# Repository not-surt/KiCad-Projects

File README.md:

# KiCad-Projects

CC0 unless otherwise stated in subdirectory.

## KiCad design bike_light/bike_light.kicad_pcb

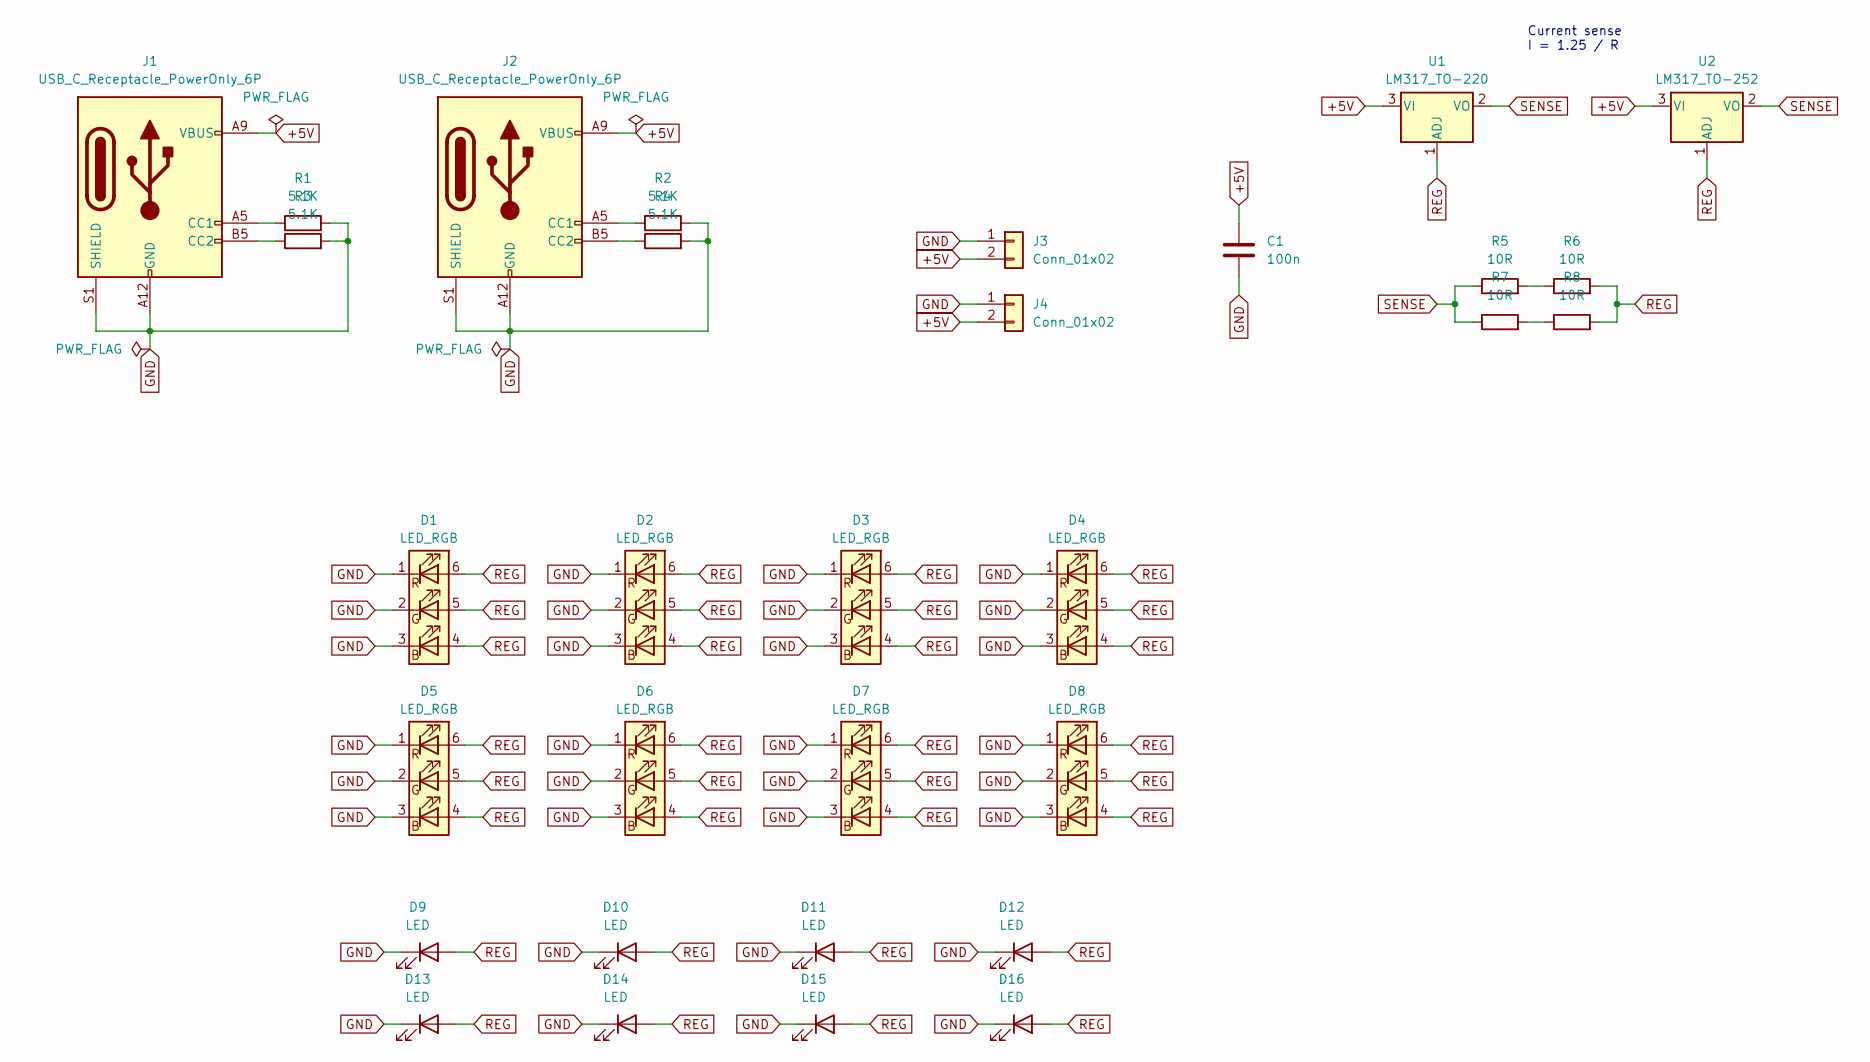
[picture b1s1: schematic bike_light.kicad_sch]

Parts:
C1: 100n; C_0805_2012Metric_Pad1.18x1.45mm_HandSolder
D1, D2, D3, D4, D5, D6, D7, D8: LED_RGB; LED_RGB_5050-6
D9, D10, D11, D12, D13, D14, D15, D16: LED; LED_Rectangular_W7.62mm_H4.55mm_P5.08mm_R3
J1, J2: USB_C_Receptacle_PowerOnly_6P; TYPE-C-31-M-17_handsolder
J3, J4: Conn_01x02; SolderWire-0.75sqmm_1x02_P4.8mm_D1.25mm_OD2.3mm_Relief
R1, R2, R3, R4: 5.1K; R_0805_2012Metric_Pad1.20x1.40mm_HandSolder
R5, R6, R7, R8: 10R; R_0805_2012Metric_Pad1.20x1.40mm_HandSolder
U1: LM317_TO-220; TO-220-3_Horizontal_TabDown
U2: LM317_TO-252; TO-252-2

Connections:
+5V: C1.1, J1.A9 (VBUS), J1.B9 (VBUS), J2.A9 (VBUS), J2.B9 (VBUS), J3.2, J4.2, U1.3 (VI), U2.3 (VI)
GND: C1.2, D1.1 (RK), D1.2 (GK), D1.3 (BK), D2.1 (RK), D2.2 (GK), D2.3 (BK), D3.1 (RK), D3.2 (GK), D3.3 (BK), D4.1 (RK), D4.2 (GK), D4.3 (BK), D5.1 (RK), D5.2 (GK), D5.3 (BK), D6.1 (RK), D6.2 (GK), D6.3 (BK), D7.1 (RK), D7.2 (GK), D7.3 (BK), D8.1 (RK), D8.2 (GK), D8.3 (BK), D9.1 (K), D10.1 (K), D11.1 (K), D12.1 (K), D13.1 (K), D14.1 (K), D15.1 (K), D16.1 (K), J1.A12 (GND), J1.B12 (GND), J1.S1 (SHIELD), J2.A12 (GND), J2.B12 (GND), J2.S1 (SHIELD), J3.1, J4.1, R1.2, R2.2, R3.2, R4.2
unnamed: J1.A5 (CC1), R1.1
unnamed: J1.B5 (CC2), R3.1
unnamed: J2.A5 (CC1), R2.1
unnamed: J2.B5 (CC2), R4.1
unnamed: R5.2, R6.1
unnamed: R7.2, R8.1
REG: D1.4 (BA), D1.5 (GA), D1.6 (RA), D2.4 (BA), D2.5 (GA), D2.6 (RA), D3.4 (BA), D3.5 (GA), D3.6 (RA), D4.4 (BA), D4.5 (GA), D4.6 (RA), D5.4 (BA), D5.5 (GA), D5.6 (RA), D6.4 (BA), D6.5 (GA), D6.6 (RA), D7.4 (BA), D7.5 (GA), D7.6 (RA), D8.4 (BA), D8.5 (GA), D8.6 (RA), D9.2 (A), D10.2 (A), D11.2 (A), D12.2 (A), D13.2 (A), D14.2 (A), D15.2 (A), D16.2 (A), R6.2, R8.2, U1.1 (ADJ), U2.1 (ADJ)
SENSE: R5.1, R7.1, U1.2 (VO), U2.2 (VO)

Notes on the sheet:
Current sense I = 1.25 / R

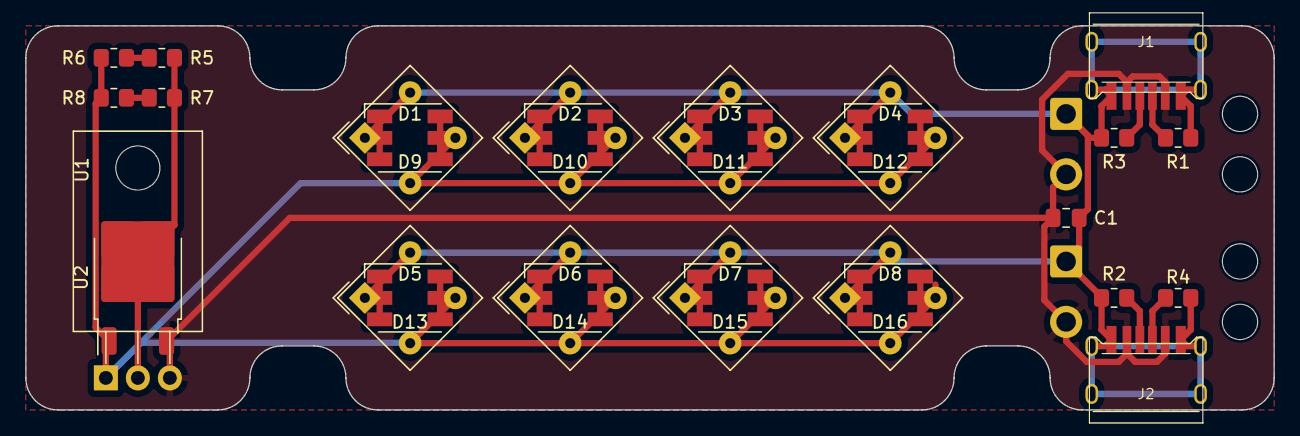
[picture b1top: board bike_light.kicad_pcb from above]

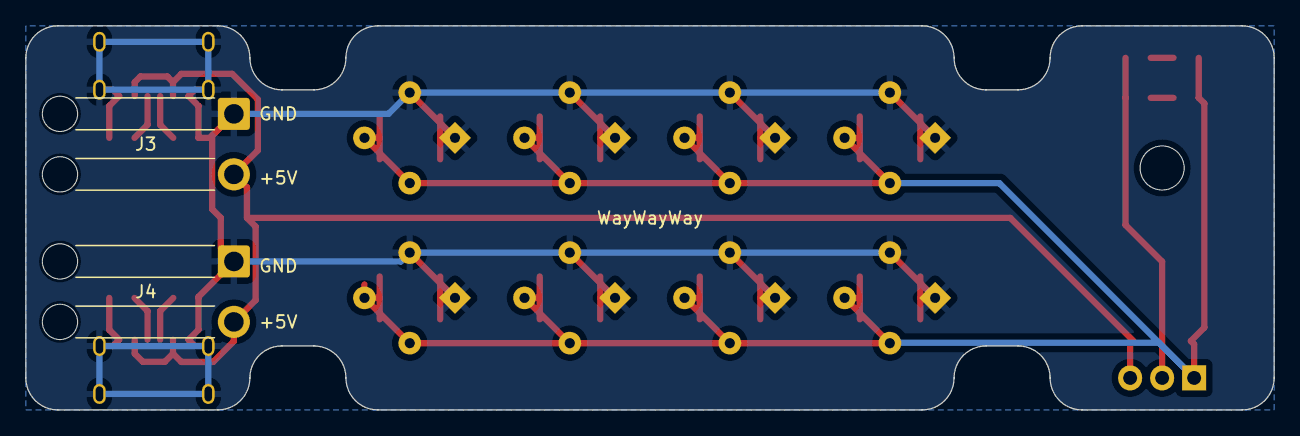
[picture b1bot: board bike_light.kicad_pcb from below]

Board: 2 copper layers, 99.1 x 30.5 mm, 31 parts (2 on the bottom side), 10 nets.

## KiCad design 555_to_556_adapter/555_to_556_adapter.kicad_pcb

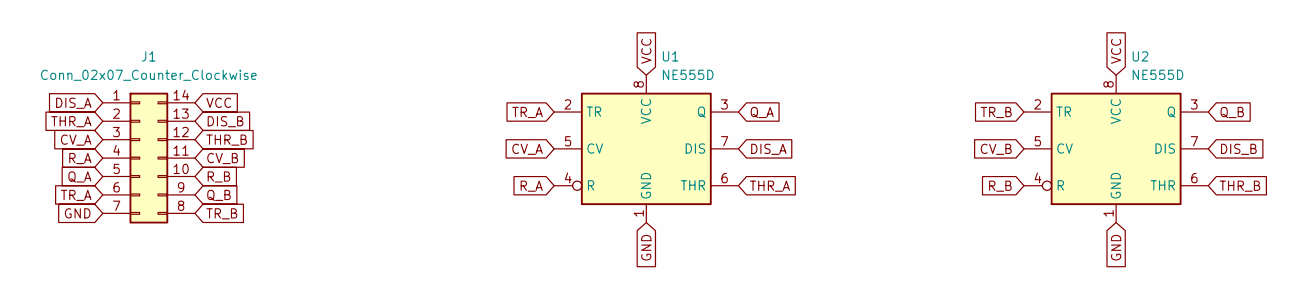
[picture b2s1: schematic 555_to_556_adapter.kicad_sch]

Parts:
J1: Conn_02x07_Counter_Clockwise; DIP-14_W7.62mm_Socket
U1, U2: NE555D; SOIC-8_3.9x4.9mm_P1.27mm

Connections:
CV_A: J1.3, U1.5 (CV)
CV_B: J1.11, U2.5 (CV)
DIS_A: J1.1, U1.7 (DIS)
DIS_B: J1.13, U2.7 (DIS)
GND: J1.7, U1.1 (GND), U2.1 (GND)
Q_A: J1.5, U1.3 (Q)
Q_B: J1.9, U2.3 (Q)
R_A: J1.4, U1.4 (R)
R_B: J1.10, U2.4 (R)
THR_A: J1.2, U1.6 (THR)
THR_B: J1.12, U2.6 (THR)
TR_A: J1.6, U1.2 (TR)
TR_B: J1.8, U2.2 (TR)
VCC: J1.14, U1.8 (VCC), U2.8 (VCC)

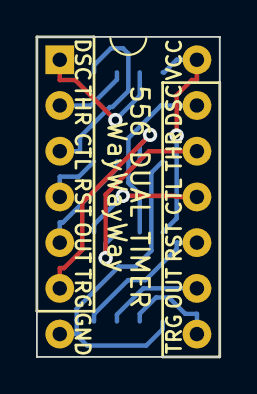
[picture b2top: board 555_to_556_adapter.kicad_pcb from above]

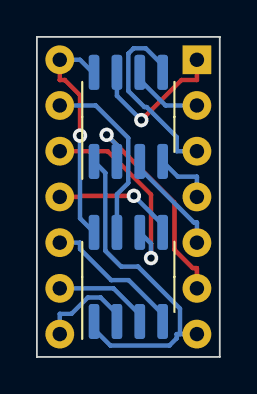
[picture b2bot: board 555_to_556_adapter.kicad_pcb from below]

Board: 2 copper layers, 10.2 x 17.8 mm, 3 parts (2 on the bottom side), 14 nets.

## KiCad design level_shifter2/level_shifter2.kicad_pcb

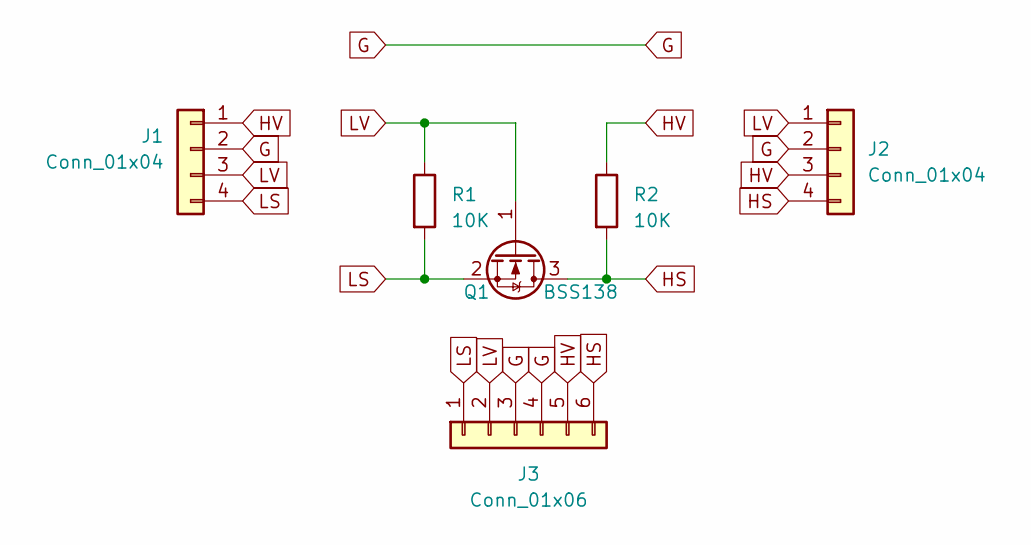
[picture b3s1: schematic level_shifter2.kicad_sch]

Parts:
J1, J2: Conn_01x04; PinHeader_1x04_P2.54mm_Vertical_no_silk
J3: Conn_01x06; PinHeader_1x06_P2.54mm_Vertical_no_silk
Q1: BSS138; SOT-23_Handsoldering
R1, R2: 10K; R_0805_2012Metric_Pad1.20x1.40mm_HandSolder

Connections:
G: J1.2, J2.2, J3.3, J3.4
HS: J2.4, J3.6, Q1.3 (D), R2.2
HV: J1.1, J2.3, J3.5, R2.1
LS: J1.4, J3.1, Q1.2 (S), R1.2
LV: J1.3, J2.1, J3.2, Q1.1 (G), R1.1

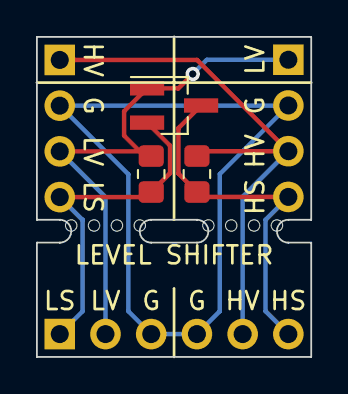
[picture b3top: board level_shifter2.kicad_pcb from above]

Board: 2 copper layers, 15.2 x 17.8 mm, 6 parts (0 on the bottom side), 5 nets.

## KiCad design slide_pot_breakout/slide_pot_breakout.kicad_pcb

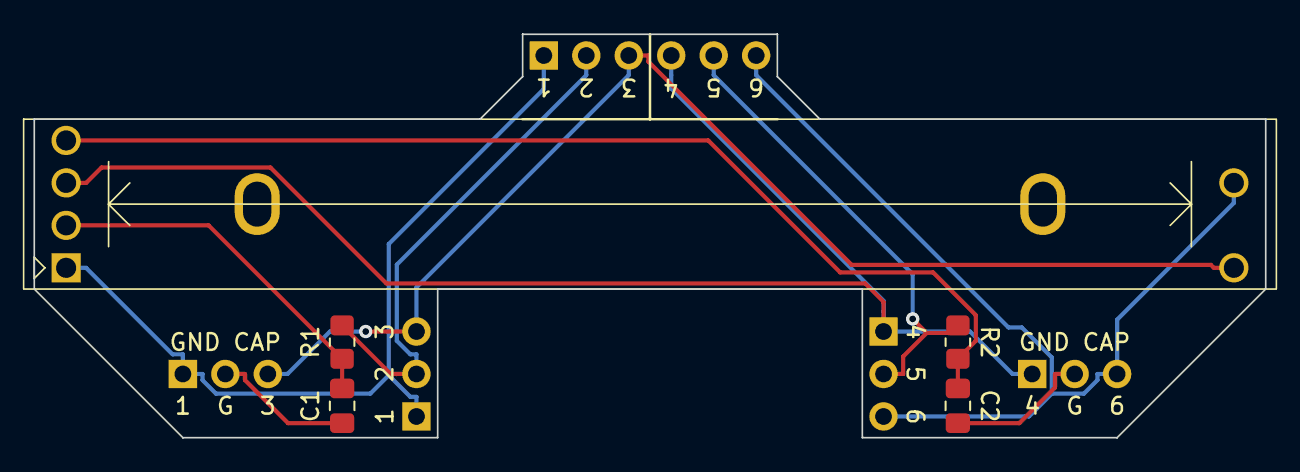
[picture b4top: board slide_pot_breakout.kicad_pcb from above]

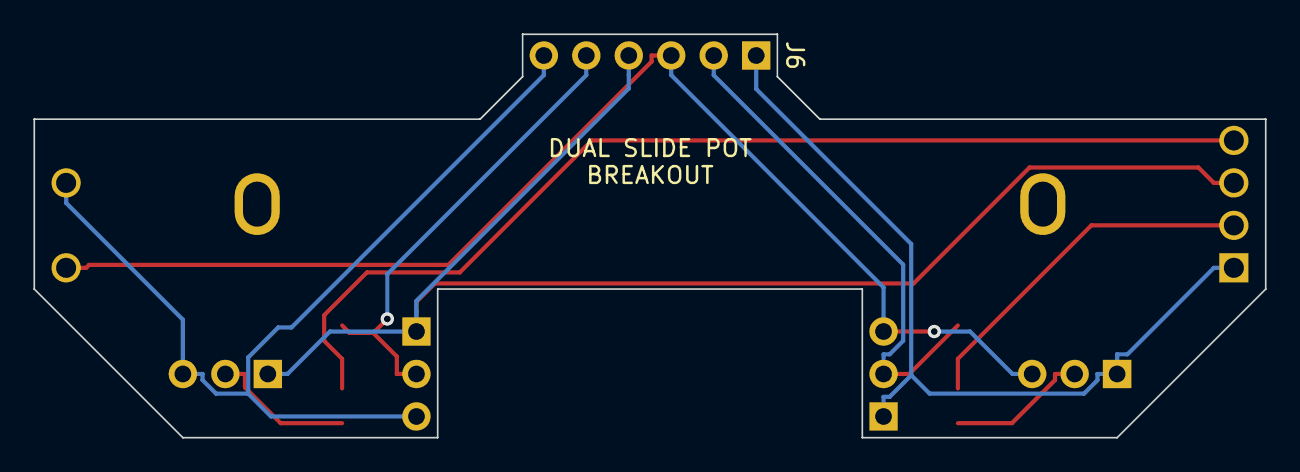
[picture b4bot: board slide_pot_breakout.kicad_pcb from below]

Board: 2 copper layers, 73.7 x 24.1 mm, 10 parts (3 on the bottom side), 10 nets.

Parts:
C1, C2: 1uF; C_0805_2012Metric_Pad1.18x1.45mm_HandSolder
J1, J2, J3, J4: Conn_01x03; PinHeader_1x03_P2.54mm_Vertical_no_silk
J6: Conn_01x06; PinHeader_1x06_P2.54mm_Vertical_no_silk
R1, R2: 0R; R_0805_2012Metric_Pad1.20x1.40mm_HandSolder
RV1: R_Potentiometer_Dual; Potentiometer_60mm_Travel_Dual_Slide

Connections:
1: J1.1 (A), J3.1, J6.1, RV1.1
2: J3.2, J6.2, R1.2
3: J1.3 (B), J3.3, J6.3, RV1.3
4: J2.1 (A), J4.1, J6.4, RV1.4
5: J4.2, J6.5, R2.1
6: J2.3 (B), J4.3, J6.6, RV1.6
LOUT: C1.1, R1.1, RV1.2
unnamed: C1.2, J1.2 (C)
unnamed: C2.2, J2.2 (C)
ROUT: C2.1, R2.2, RV1.5

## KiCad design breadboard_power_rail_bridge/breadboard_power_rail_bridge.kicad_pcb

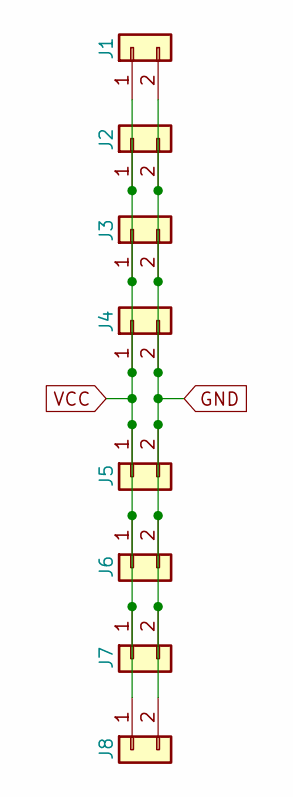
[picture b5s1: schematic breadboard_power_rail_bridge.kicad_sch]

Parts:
J1, J2, J3, J4, J5, J6, J7, J8: Conn_01x02; PinHeader_1x02_P2.54mm_Vertical_edited

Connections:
GND: J1.2, J2.2, J3.2, J4.2, J5.2, J6.2, J7.2, J8.2
VCC: J1.1, J2.1, J3.1, J4.1, J5.1, J6.1, J7.1, J8.1

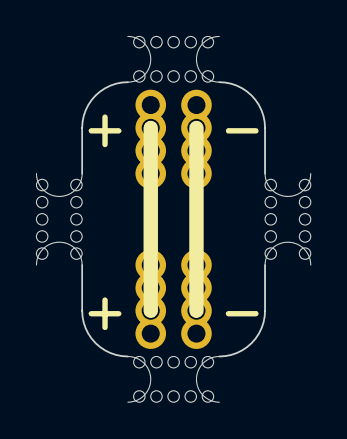
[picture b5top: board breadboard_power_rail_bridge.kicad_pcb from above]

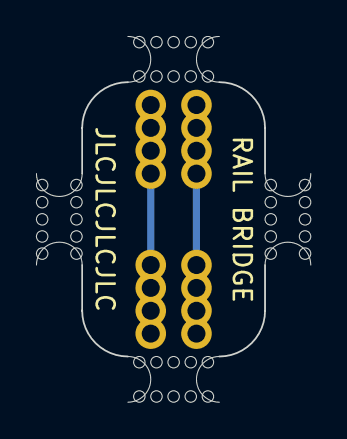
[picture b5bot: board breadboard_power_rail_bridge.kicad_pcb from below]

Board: 2 copper layers, 15.2 x 20.3 mm, 8 parts (8 on the bottom side), 2 nets.

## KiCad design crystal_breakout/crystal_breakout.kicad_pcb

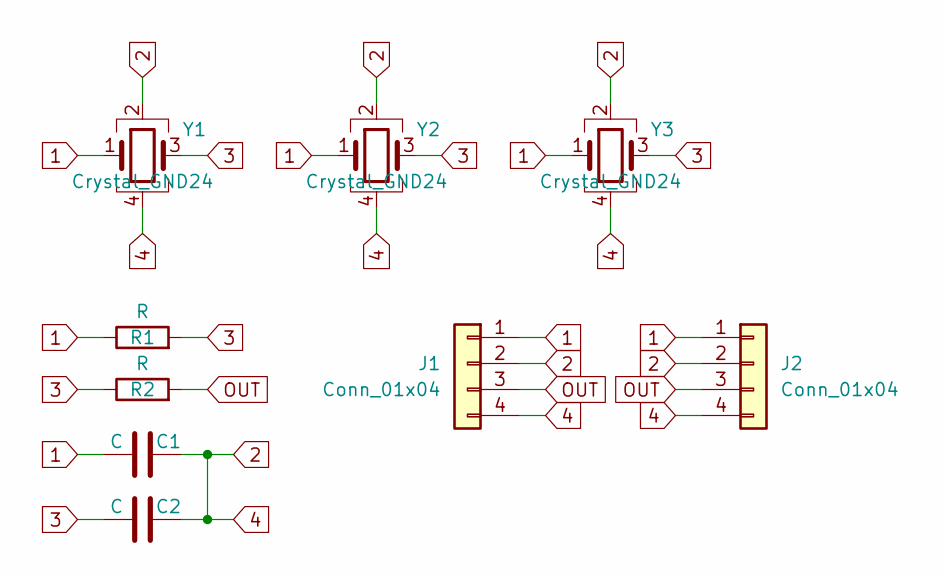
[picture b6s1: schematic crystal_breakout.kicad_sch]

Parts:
C1, C2: C; C_0805_2012Metric_Pad1.18x1.45mm_HandSolder
J1, J2: Conn_01x04; PinHeader_1x04_P2.54mm_Vertical
R1, R2: R; R_0805_2012Metric_Pad1.20x1.40mm_HandSolder
Y1: Crystal_GND24; Crystal_SMD_7050-4Pin_7.0x5.0mm
Y2: Crystal_GND24; Crystal_SMD_5032-4Pin_5.0x3.2mm
Y3: Crystal_GND24; Crystal_SMD_3225-4Pin_3.2x2.5mm

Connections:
1: C1.1, J1.1, J2.1, R1.1, Y1.1, Y2.1, Y3.1
2: C1.2, C2.2, J1.2, J1.4, J2.2, J2.4, Y1.2, Y1.4, Y2.2, Y2.4, Y3.2, Y3.4
3: C2.1, R1.2, R2.1, Y1.3, Y2.3, Y3.3
OUT: J1.3, J2.3, R2.2

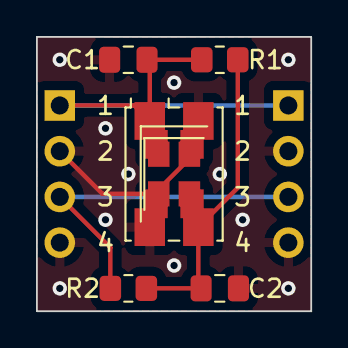
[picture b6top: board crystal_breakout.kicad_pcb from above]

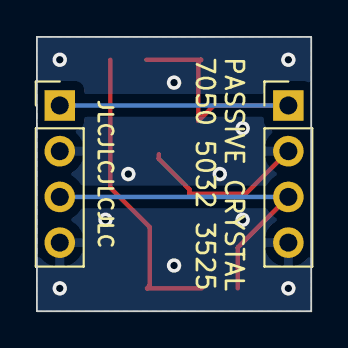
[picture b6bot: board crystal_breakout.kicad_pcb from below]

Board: 2 copper layers, 15.2 x 15.2 mm, 9 parts (2 on the bottom side), 4 nets.

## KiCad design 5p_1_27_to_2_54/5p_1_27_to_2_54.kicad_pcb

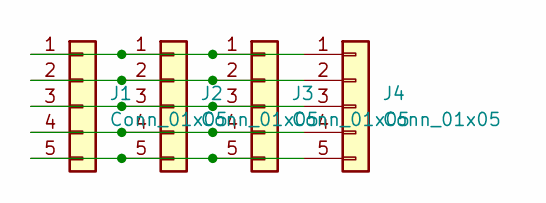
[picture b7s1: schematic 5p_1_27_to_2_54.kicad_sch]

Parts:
J1, J2: Conn_01x05; PinHeader_1x05_P1.27mm_Vertical_stretch
J3, J4: Conn_01x05; PinHeader_1x05_P2.54mm_Vertical_stretch

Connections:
unnamed: J1.1, J2.1, J3.1, J4.1
unnamed: J1.2, J2.2, J3.2, J4.2
unnamed: J1.3, J2.3, J3.3, J4.3
unnamed: J1.4, J2.4, J3.4, J4.4
unnamed: J1.5, J2.5, J3.5, J4.5

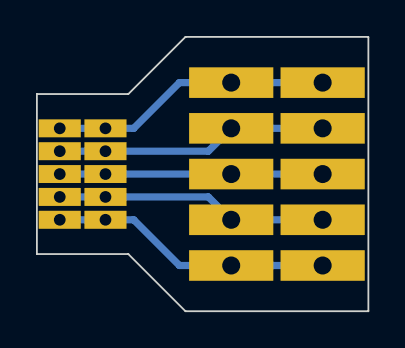
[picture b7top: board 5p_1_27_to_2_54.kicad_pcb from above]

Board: 2 copper layers, 18.4 x 15.2 mm, 4 parts (0 on the bottom side), 5 nets.

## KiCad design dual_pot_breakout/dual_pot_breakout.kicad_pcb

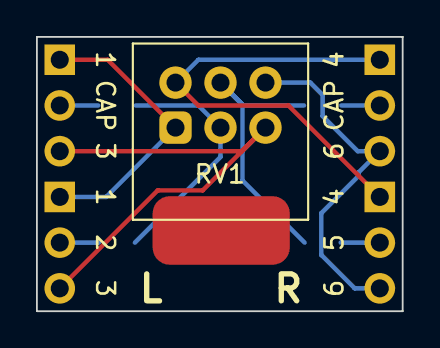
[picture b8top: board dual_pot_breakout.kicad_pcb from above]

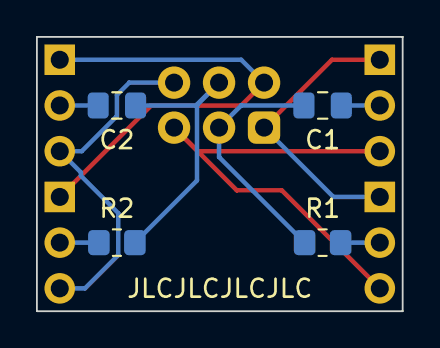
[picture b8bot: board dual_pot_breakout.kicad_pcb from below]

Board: 2 copper layers, 20.3 x 15.2 mm, 9 parts (6 on the bottom side), 10 nets.

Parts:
C1, C2: 1uF; C_0805_2012Metric_Pad1.18x1.45mm_HandSolder
J1, J2, J3, J4: Conn_01x03; PinHeader_1x03_P2.54mm_Vertical_no_silk
R1, R2: 0R; R_0805_2012Metric_Pad1.20x1.40mm_HandSolder
RV1: R_Potentiometer_Dual; Potentiometer_Alps_RK097_Dual_Horizontal

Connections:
1: J1.1 (A), J3.1, RV1.1
2: C1.1, R1.1, RV1.2
3: J1.3 (B), J3.3, RV1.3
4: J2.1 (A), J4.1, RV1.4
5: C2.1, R2.1, RV1.5
6: J2.3 (B), J4.3, RV1.6
unnamed: C1.2, J1.2 (C)
unnamed: C2.2, J2.2 (C)
unnamed: J3.2, R1.2
unnamed: J4.2, R2.2

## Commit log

2023-01-15 Initial commit.
2023-01-15 Make smd led adaptor cathode/anode commonable.
2023-01-16 More stuff.
2023-01-21 Add dipa.
2023-01-21 Add more.
2023-01-28 Finished.
2023-01-28 Add hub75_multi_mcu.
2023-01-28 Fix hub75_multi_mcu file names.
2023-01-30 Add muli-expansion_board3.
2023-01-30 A few tweaks to multi_expansion_board3.
2023-02-25 New revision of WS8211 Dumb Adaptor.
2023-02-26 Multi Expansion Board revision 4.
2023-06-21 Add .gitignore.
2023-06-21 Misc.
2023-06-21 More misc.
2023-06-21 Spelling.
2023-11-04 Added bike light.
2023-11-04 Added 555 to 556 adapter.
2023-11-05 Finish bike light.
